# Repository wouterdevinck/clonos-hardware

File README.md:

#Clonos
**Open source network audio player**
by Wouter Devinck

##Repositories
 * **Hardware** (block diagram, schematic, pcb layout, ...): <br />
   https://github.com/wouterdevinck/clonos-hardware
 * Software (QT application, GStreamer interaction, ...): <br />
   https://github.com/wouterdevinck/clonos-application
 * Build system (Buildroot configuration files, kernel configuration, ...): <br />
   https://github.com/wouterdevinck/clonos-build
 * Android app: <br />
   https://github.com/wouterdevinck/clonos-android
 * Efforts to reverse engineer Spotify Connect: <br />
   https://github.com/wouterdevinck/clonos-poc-spotify

##Block diagram

##Prototype
*Status: boards ordered (December 1, 2015)*

Stack of four boards with all the components that have to end up on the final board.

###Protostack CPU
https://workspace.circuitmaker.com/Projects/B66F455D-E0F4-4F57-BF12-8FCD42A89455

###Protostack Power
https://workspace.circuitmaker.com/Projects/ADCA47EF-8110-4858-A632-40D1FB39EC8E

###Protostack Audio
https://workspace.circuitmaker.com/Projects/CEEC1620-CD76-49D0-8387-5E8A08206CBC

###Protostack Wifi
https://workspace.circuitmaker.com/Projects/3BDADFC3-9059-4C72-BE22-5D24FC84C105

##Final board
*Status: board design in progress*
https://workspace.circuitmaker.com/Projects/203E8A99-4B7F-4577-A6F3-57C3B201C072

##License
<br />This **hardware design** is licensed under a <a rel="license" href="http://creativecommons.org/licenses/by-sa/4.0/">Creative Commons Attribution-ShareAlike 4.0 International License</a>.

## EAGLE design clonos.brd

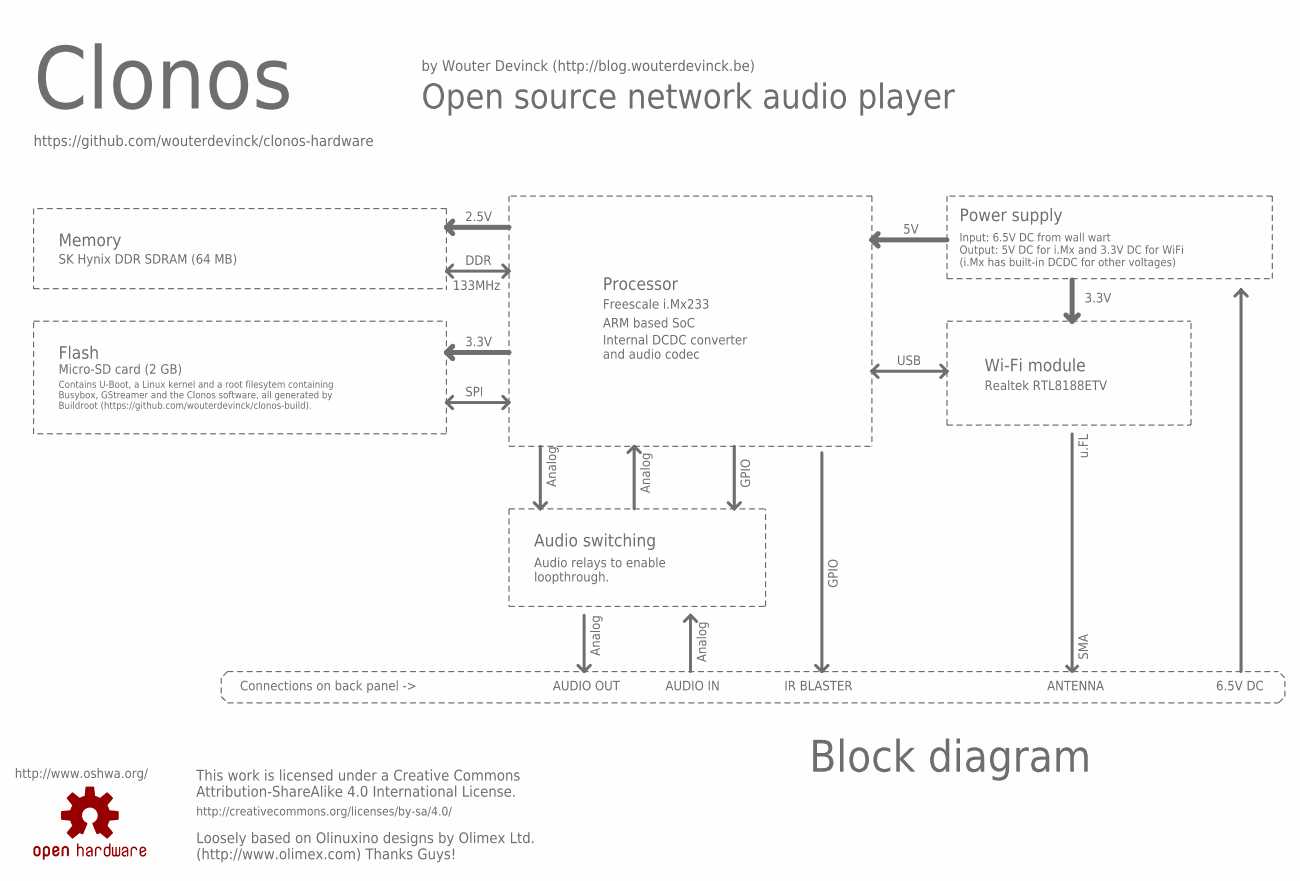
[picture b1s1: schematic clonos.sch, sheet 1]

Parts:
LOGO1: OSHW-LOGOS; OSHW-LOGO-S

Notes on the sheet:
Block diagram
Clonos
This work is licensed under a Creative Commons Attribution-ShareAlike 4.0 International License.
http://creativecommons.org/licenses/by-sa/4.0/
Open source network audio player
https://github.com/wouterdevinck/clonos-hardware
Loosely based on Olinuxino designs by Olimex Ltd. (http://www.olimex.com) Thanks Guys!
by Wouter Devinck (http://blog.wouterdevinck.be)
Power supply
Input: 6.5V DC from wall wart Output: 5V DC for i.Mx and 3.3V DC for WiFi (i.Mx has built-in DCDC for other voltages)
Processor
Freescale i.Mx233
Wi-Fi module
Flash
Memory
Audio switching
Realtek RTL8188ETV
Micro-SD card (2 GB)
Contains U-Boot, a Linux kernel and a root filesytem containing Busybox, GStreamer and the Clonos software, all generated by Buildroot (https://github.com/wouterdevinck/clonos-build).
SK Hynix DDR SDRAM (64 MB)
Audio relays to enable loopthrough.
6.5V DC
ANTENNA
IR BLASTER
AUDIO OUT
AUDIO IN
3.3V
USB
GPIO
Analog
2.5V
SPI
DDR
133MHz
Connections on back panel ->
u.FL
SMA
ARM based SoC
Internal DCDC converter and audio codec
http://www.oshwa.org/

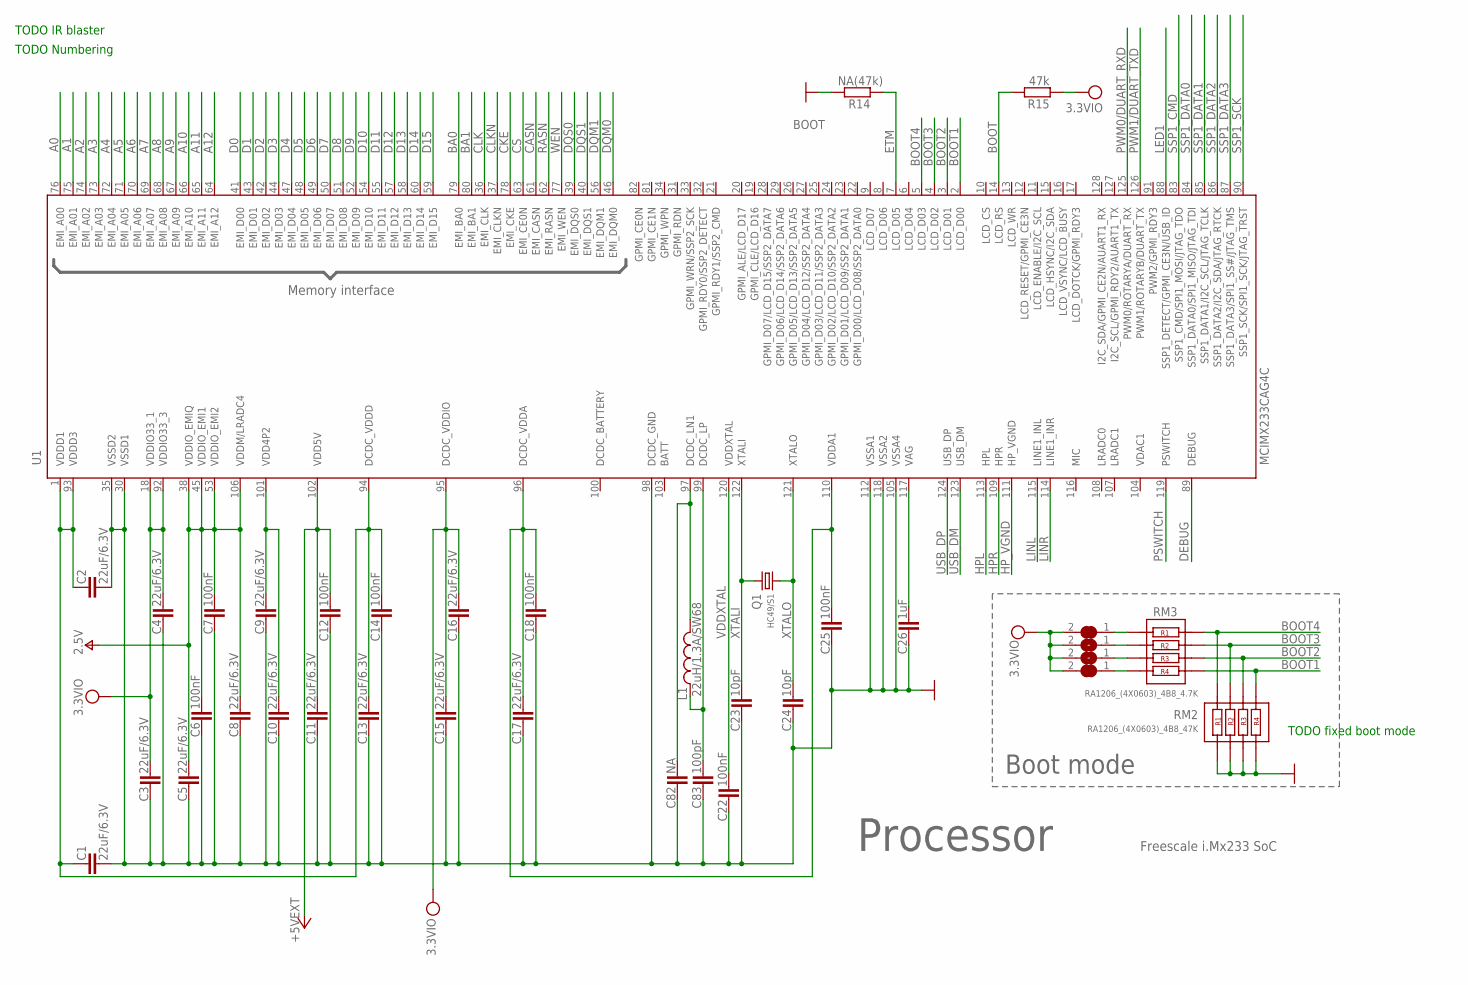
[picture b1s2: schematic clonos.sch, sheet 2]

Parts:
C1, C2, C3, C4, C5, C8, C9, C10, C11, C13, C15, C16, C17: 22uF/6.3V; C0805_5MIL_DWS
C6, C7, C12, C14, C18, C22, C25: 100nF; C0603_DWS
C23, C24: 10pF; C0603_DWS
C26: 1uF; C0603_DWS
C82: NA; C0603_DWS
C83: 100pF; C0603_DWS
D00_H, D03_H: Close; SJ_1_SMALLER
D01_H, D02_H: Open; SJ_1_SMALLER
L1: 22uH/1.3A/SW68; CD53
Q1: HC49/S1; HC49/SMD2_THIN
R14: NA(47k); R0603_5MIL_DWS
R15: 47k; R0603_5MIL_DWS
RM2: RA1206_(4X0603)_4B8_47K; R_MATRIX_4
RM3: RA1206_(4X0603)_4B8_4.7K; R_MATRIX_4
U1: MCIMX233CAG4C; TQFP128LD

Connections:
+5V: C11.2, C12.2, U1.102 (VDD5V); also elsewhere on the board
A0: U1.76 (EMI_A00); also elsewhere on the board
A1: U1.75 (EMI_A01); also elsewhere on the board
A2: U1.74 (EMI_A02); also elsewhere on the board
A3: U1.73 (EMI_A03); also elsewhere on the board
A4: U1.72 (EMI_A04); also elsewhere on the board
A5: U1.71 (EMI_A05); also elsewhere on the board
A6: U1.70 (EMI_A06); also elsewhere on the board
A7: U1.69 (EMI_A07); also elsewhere on the board
A8: U1.68 (EMI_A08); also elsewhere on the board
A9: U1.67 (EMI_A09); also elsewhere on the board
A10: U1.66 (EMI_A10); also elsewhere on the board
A11: U1.65 (EMI_A11); also elsewhere on the board
A12: U1.64 (EMI_A12); also elsewhere on the board
BA0: U1.79 (EMI_BA0); also elsewhere on the board
BA1: U1.80 (EMI_BA1); also elsewhere on the board
BOOT: R15.2, U1.14 (LCD_RS)
BOOT1: RM2.4.2, RM3.4.1, U1.2 (LCD_D00)
BOOT2: RM2.3.2, RM3.3.1, U1.3 (LCD_D01)
BOOT3: RM2.2.2, RM3.2.1, U1.4 (LCD_D02)
BOOT4: RM2.1.2, RM3.1.1, U1.5 (LCD_D03)
CASN: U1.61 (EMI_CASN); also elsewhere on the board
CKE: U1.78 (EMI_CKE); also elsewhere on the board
CLK: U1.36 (EMI_CLK); also elsewhere on the board
CLKN: U1.37 (EMI_CLKN); also elsewhere on the board
CS: U1.63 (EMI_CE0N); also elsewhere on the board
D0: U1.41 (EMI_D00); also elsewhere on the board
D1: U1.43 (EMI_D01); also elsewhere on the board
D2: U1.42 (EMI_D02); also elsewhere on the board
D3: U1.44 (EMI_D03); also elsewhere on the board
D4: U1.47 (EMI_D04); also elsewhere on the board
D5: U1.48 (EMI_D05); also elsewhere on the board
D6: U1.49 (EMI_D06); also elsewhere on the board
D7: U1.50 (EMI_D07); also elsewhere on the board
D8: U1.51 (EMI_D08); also elsewhere on the board
D9: U1.52 (EMI_D09); also elsewhere on the board
D10: U1.54 (EMI_D10); also elsewhere on the board
D11: U1.55 (EMI_D11); also elsewhere on the board
D12: U1.57 (EMI_D12); also elsewhere on the board
D13: U1.58 (EMI_D13); also elsewhere on the board
D14: U1.60 (EMI_D14); also elsewhere on the board
D15: U1.59 (EMI_D15); also elsewhere on the board
DCDC_BATTERY: U1.100 (DCDC_BATTERY)
DCDC_VDDA: C17.2, C18.2, C25.2, U1.96 (DCDC_VDDA), U1.110 (VDDA1)
DCDC_VDDD: C1.2, C2.2, C13.2, C14.2, U1.1 (VDDD1), U1.93 (VDDD3), U1.94 (DCDC_VDDD)
DEBUG: U1.89 (DEBUG); also elsewhere on the board
DQM0: U1.46 (EMI_DQM0); also elsewhere on the board
DQM1: U1.56 (EMI_DQM1); also elsewhere on the board
DQS0: U1.39 (EMI_DQS0); also elsewhere on the board
DQS1: U1.40 (EMI_DQS1); also elsewhere on the board
ETM: R14.2, U1.7 (LCD_D05)
GND: C1.1, C2.1, C3.1, C4.1, C5.1, C6.1, C7.1, C8.1, C9.1, C10.1, C11.1, C12.1, C13.1, C14.1, C15.1, C16.1, C17.1, C18.1, C22.1, C23.1, C24.1, C25.1, C26.1, C82.1, C83.1, R14.1, RM2.1.1, RM2.2.1, RM2.3.1, RM2.4.1, U1.30 (VSSD1), U1.35 (VSSD2), U1.98 (DCDC_GND), U1.105 (VSSA4), U1.112 (VSSA1), U1.118 (VSSA2); also elsewhere on the board
HPL: U1.113 (HPL); also elsewhere on the board
HPR: U1.109 (HPR); also elsewhere on the board
HP_VGND: U1.111 (HP_VGND); also elsewhere on the board
LED1: U1.88 (SSP1_DETECT/GPMI_CE3N/USB_ID); also elsewhere on the board
LINL: U1.115 (LINE1_INL); also elsewhere on the board
LINR: U1.114 (LINE1_INR); also elsewhere on the board
unnamed: C82.2, L1.2, U1.97 (DCDC_LN1)
unnamed: C83.2, L1.1, U1.99 (DCDC_LP)
unnamed: C26.2, U1.117 (VAG)
unnamed: D03_H.1, RM3.1.2
unnamed: D02_H.1, RM3.2.2
unnamed: D01_H.1, RM3.3.2
unnamed: D00_H.1, RM3.4.2
PSWITCH: U1.119 (PSWITCH); also elsewhere on the board
PWM0/DUART_RXD: U1.125 (PWM0/ROTARYA/DUART_RX); also elsewhere on the board
PWM1/DUART_TXD: U1.126 (PWM1/ROTARYB/DUART_TX); also elsewhere on the board
RASN: U1.62 (EMI_RASN); also elsewhere on the board
SSP1_CMD: U1.83 (SSP1_CMD/SPI1_MOSI/JTAG_TDO); also elsewhere on the board
SSP1_DATA0: U1.84 (SSP1_DATA0/SPI1_MISO/JTAG_TDI); also elsewhere on the board
SSP1_DATA1: U1.85 (SSP1_DATA1/I2C_SCL/JTAG_TCLK); also elsewhere on the board
SSP1_DATA2: U1.86 (SSP1_DATA2/I2C_SDA/JTAG_RTCK); also elsewhere on the board
SSP1_DATA3: U1.87 (SSP1_DATA3/SPI1_SS#/JTAG_TMS); also elsewhere on the board
SSP1_SCK: U1.90 (SSP1_SCK/SPI1_SCK/JTAG_TRST); also elsewhere on the board
USB_DM: U1.123 (USB_DM); also elsewhere on the board
USB_DP: U1.124 (USB_DP); also elsewhere on the board
V+: C5.2, C6.2, C7.2, C8.2, U1.38 (VDDIO_EMIQ), U1.45 (VDDIO_EMI1), U1.53 (VDDIO_EMI2), U1.106 (VDDM/LRADC4); also elsewhere on the board
VDD4P2: C9.2, C10.2, U1.101 (VDD4P2)
VDDXTAL: C22.2, U1.120 (VDDXTAL); also elsewhere on the board
VPP: C3.2, C4.2, C15.2, C16.2, D00_H.2, D01_H.2, D02_H.2, D03_H.2, R15.1, U1.18 (VDDIO33_1), U1.92 (VDDIO33_3), U1.95 (DCDC_VDDIO); also elsewhere on the board
WEN: U1.77 (EMI_WEN); also elsewhere on the board
XTALI: C23.2, Q1.2, U1.122 (XTALI); also elsewhere on the board
XTALO: C24.2, Q1.1, U1.121 (XTALO); also elsewhere on the board

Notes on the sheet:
TODO IR blaster
TODO Numbering
Processor
Memory interface
Freescale i.Mx233 SoC
Boot mode
TODO fixed boot mode

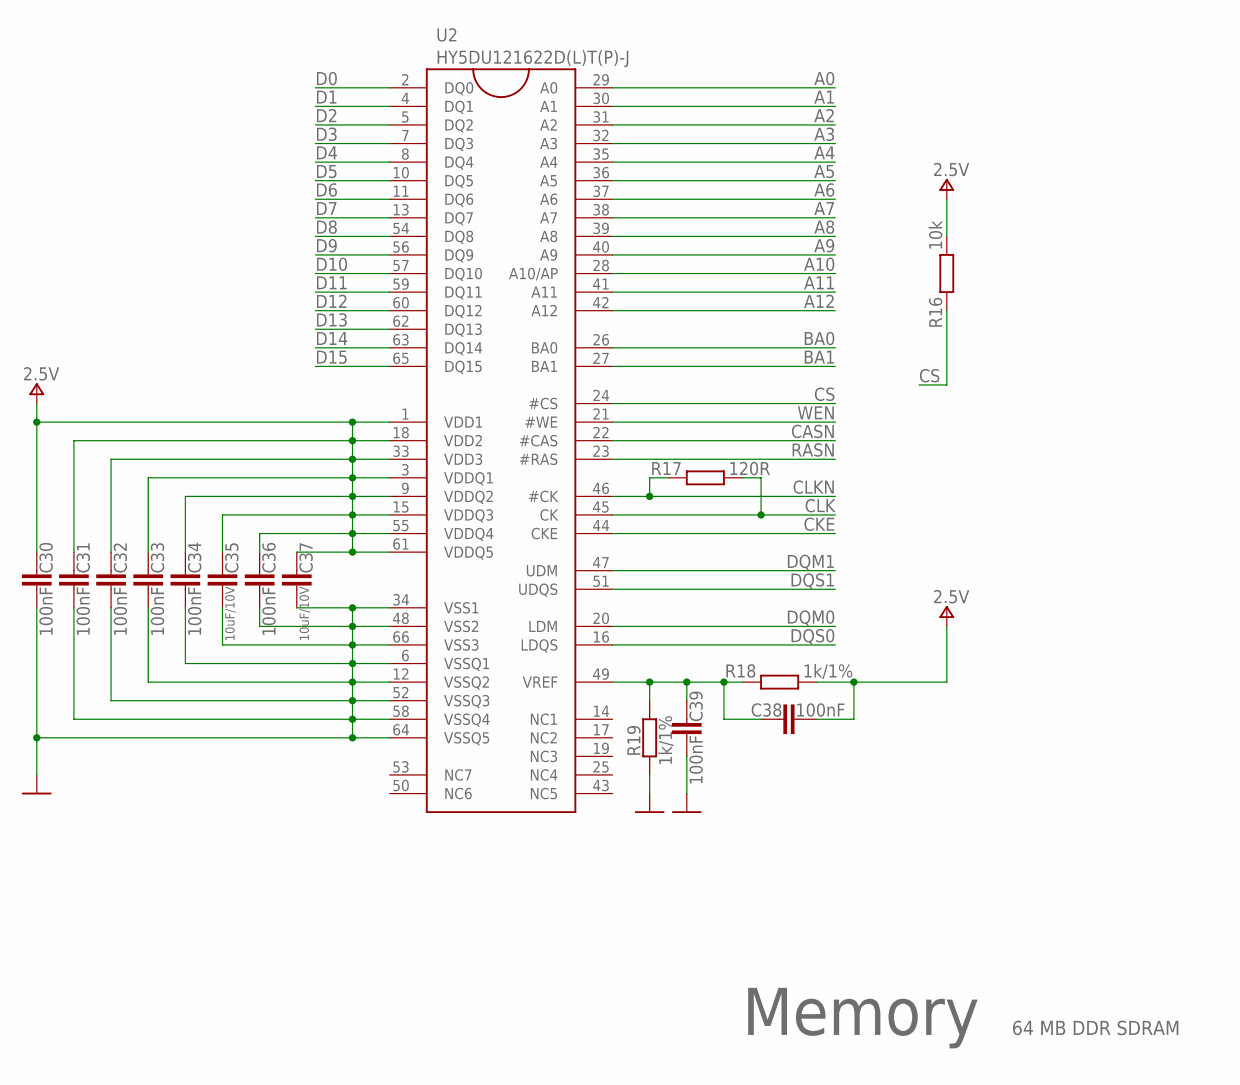
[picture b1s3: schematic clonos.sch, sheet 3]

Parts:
C30, C31, C32, C33, C34, C36, C38, C39: 100nF; C0603_DWS
C35, C37: 10uF/10V; C0603_DWS
R16: 10k; R0603_5MIL_DWS
R17: 120R; R0603_5MIL_DWS
R18, R19: 1k/1%; R0603_5MIL_DWS
U2: HY5DU121622D(L)T(P)-J; 66TSOP-II

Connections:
A0: U2.29 (A0); also elsewhere on the board
A1: U2.30 (A1); also elsewhere on the board
A2: U2.31 (A2); also elsewhere on the board
A3: U2.32 (A3); also elsewhere on the board
A4: U2.35 (A4); also elsewhere on the board
A5: U2.36 (A5); also elsewhere on the board
A6: U2.37 (A6); also elsewhere on the board
A7: U2.38 (A7); also elsewhere on the board
A8: U2.39 (A8); also elsewhere on the board
A9: U2.40 (A9); also elsewhere on the board
A10: U2.28 (A10/AP); also elsewhere on the board
A11: U2.41 (A11); also elsewhere on the board
A12: U2.42 (A12); also elsewhere on the board
BA0: U2.26 (BA0); also elsewhere on the board
BA1: U2.27 (BA1); also elsewhere on the board
CASN: U2.22 (#CAS); also elsewhere on the board
CKE: U2.44 (CKE); also elsewhere on the board
CLK: R17.2, U2.45 (CK); also elsewhere on the board
CLKN: R17.1, U2.46 (#CK); also elsewhere on the board
CS: R16.1, U2.24 (#CS); also elsewhere on the board
D0: U2.2 (DQ0); also elsewhere on the board
D1: U2.4 (DQ1); also elsewhere on the board
D2: U2.5 (DQ2); also elsewhere on the board
D3: U2.7 (DQ3); also elsewhere on the board
D4: U2.8 (DQ4); also elsewhere on the board
D5: U2.10 (DQ5); also elsewhere on the board
D6: U2.11 (DQ6); also elsewhere on the board
D7: U2.13 (DQ7); also elsewhere on the board
D8: U2.54 (DQ8); also elsewhere on the board
D9: U2.56 (DQ9); also elsewhere on the board
D10: U2.57 (DQ10); also elsewhere on the board
D11: U2.59 (DQ11); also elsewhere on the board
D12: U2.60 (DQ12); also elsewhere on the board
D13: U2.62 (DQ13); also elsewhere on the board
D14: U2.63 (DQ14); also elsewhere on the board
D15: U2.65 (DQ15); also elsewhere on the board
DQM0: U2.20 (LDM); also elsewhere on the board
DQM1: U2.47 (UDM); also elsewhere on the board
DQS0: U2.16 (LDQS); also elsewhere on the board
DQS1: U2.51 (UDQS); also elsewhere on the board
GND: C30.1, C31.1, C32.1, C33.1, C34.1, C35.1, C36.1, C37.1, C39.1, R19.1, U2.6 (VSSQ1), U2.12 (VSSQ2), U2.34 (VSS1), U2.48 (VSS2), U2.52 (VSSQ3), U2.58 (VSSQ4), U2.64 (VSSQ5), U2.66 (VSS3); also elsewhere on the board
unnamed: C38.2, C39.2, R18.1, R19.2, U2.49 (VREF)
RASN: U2.23 (#RAS); also elsewhere on the board
V+: C30.2, C31.2, C32.2, C33.2, C34.2, C35.2, C36.2, C37.2, C38.1, R16.2, R18.2, U2.1 (VDD1), U2.3 (VDDQ1), U2.9 (VDDQ2), U2.15 (VDDQ3), U2.18 (VDD2), U2.33 (VDD3), U2.55 (VDDQ4), U2.61 (VDDQ5); also elsewhere on the board
WEN: U2.21 (#WE); also elsewhere on the board

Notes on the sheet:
Memory
64 MB DDR SDRAM

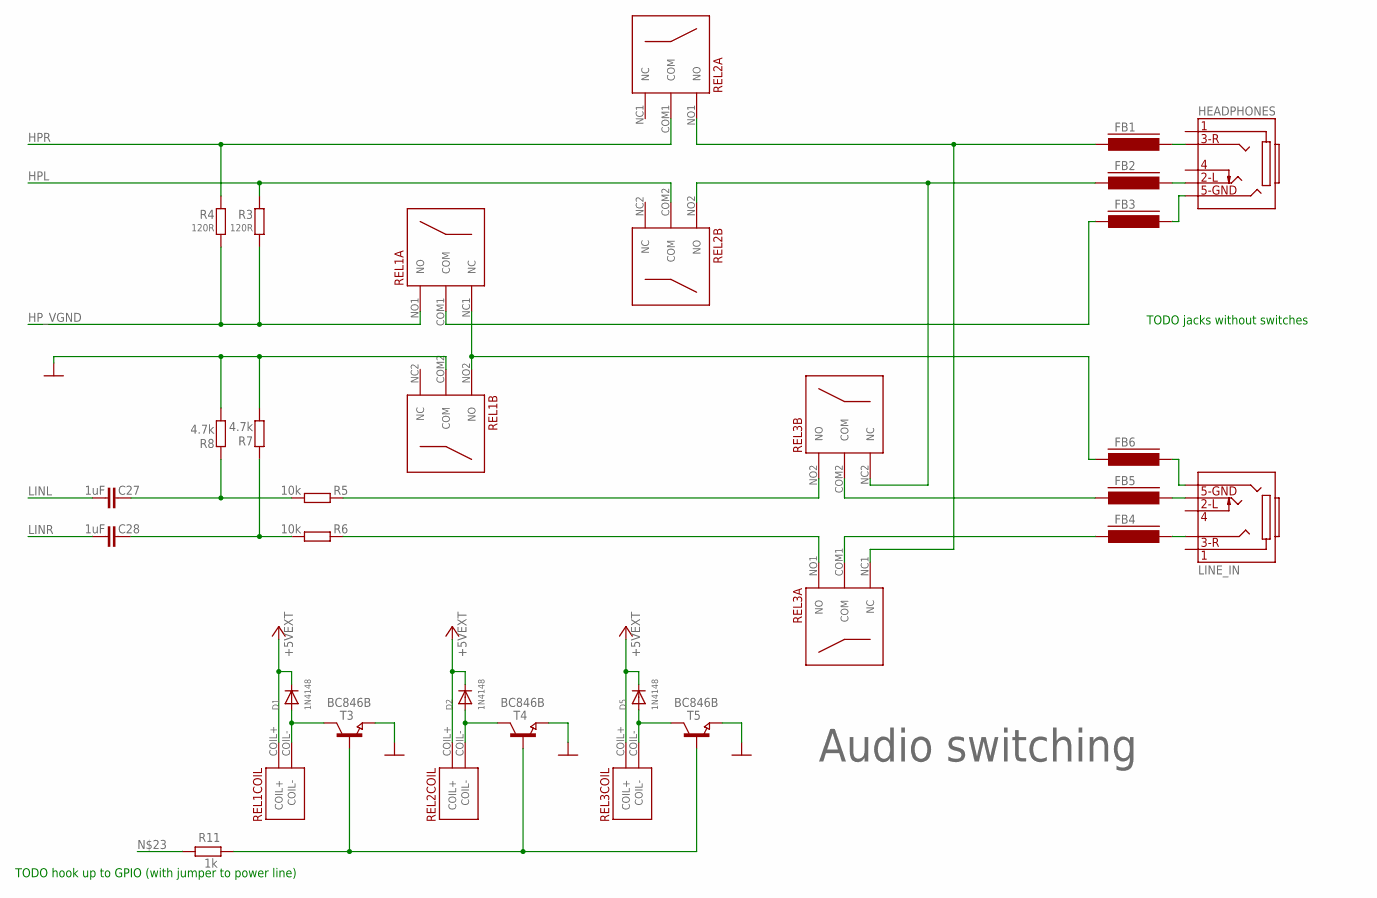
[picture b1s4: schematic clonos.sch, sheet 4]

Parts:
C27, C28: 1uF; C0603_DWS
D1, D2, D5: 1N4148; SOD-323F
FB1, FB2, FB3, FB4, FB5, FB6: HZ0805D152R; FB805
HEADPHONES: AUDIO_JACK_5PINPJ-W47S-05D2-LF_V2; PJ-W47S-05D2-LF_5PIN_V2
LINE_IN: AUDIO_JACK_5PINPJ-W47S-05D2-LF_V2; PJ-W47S-05D2-LF_5PIN_V2
R3, R4: 120R; R0603_5MIL_DWS
R5, R6: 10k; R0603_5MIL_DWS
R7, R8: 4.7k; R0603_5MIL_DWS
R11: 1k; R0603_5MIL_DWS
REL1, REL2, REL3: A5W-K-BIS; A5W-K
T3, T4, T5: BC846B; SOT23

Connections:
+5V: D1.C, D2.C, D5.C, REL1.COIL+, REL2.COIL+, REL3.COIL+; also elsewhere on the board
GND: R7.1, R8.1, REL1.COM2 (COM), T3.2 (E), T4.2 (E), T5.2 (E); also elsewhere on the board
HPL: R3.2, REL2.COM2 (COM); also elsewhere on the board
HPR: R4.2, REL2.COM1 (COM); also elsewhere on the board
HP_VGND: R3.1, R4.1, REL1.NO1 (NO); also elsewhere on the board
LINL: C27.2; also elsewhere on the board
LINR: C28.2; also elsewhere on the board
unnamed: R6.2, REL3.NO1 (NO)
unnamed: FB1.2, REL2.NO1 (NO), REL3.NC1 (NC)
unnamed: FB2.2, REL2.NO2 (NO), REL3.NC2 (NC)
unnamed: FB5.2, REL3.COM2 (COM)
unnamed: R5.2, REL3.NO2 (NO)
unnamed: FB4.2, REL3.COM1 (COM)
unnamed: FB3.2, REL1.COM1 (COM)
unnamed: FB1.1, HEADPHONES.3
unnamed: FB6.2, REL1.NC1 (NC), REL1.NO2 (NO)
unnamed: FB2.1, HEADPHONES.2
unnamed: FB3.1, HEADPHONES.5
unnamed: FB5.1, LINE_IN.2
unnamed: FB4.1, LINE_IN.3
unnamed: FB6.1, LINE_IN.5
unnamed: D1.A, REL1.COIL-, T3.3 (C)
unnamed: D2.A, REL2.COIL-, T4.3 (C)
unnamed: R11.2, T3.1 (B), T4.1 (B), T5.1 (B)
unnamed: D5.A, REL3.COIL-, T5.3 (C)
unnamed: C28.1, R6.1, R7.2
unnamed: C27.1, R5.1, R8.2

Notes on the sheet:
Audio switching
TODO jacks without switches
TODO hook up to GPIO (with jumper to power line)

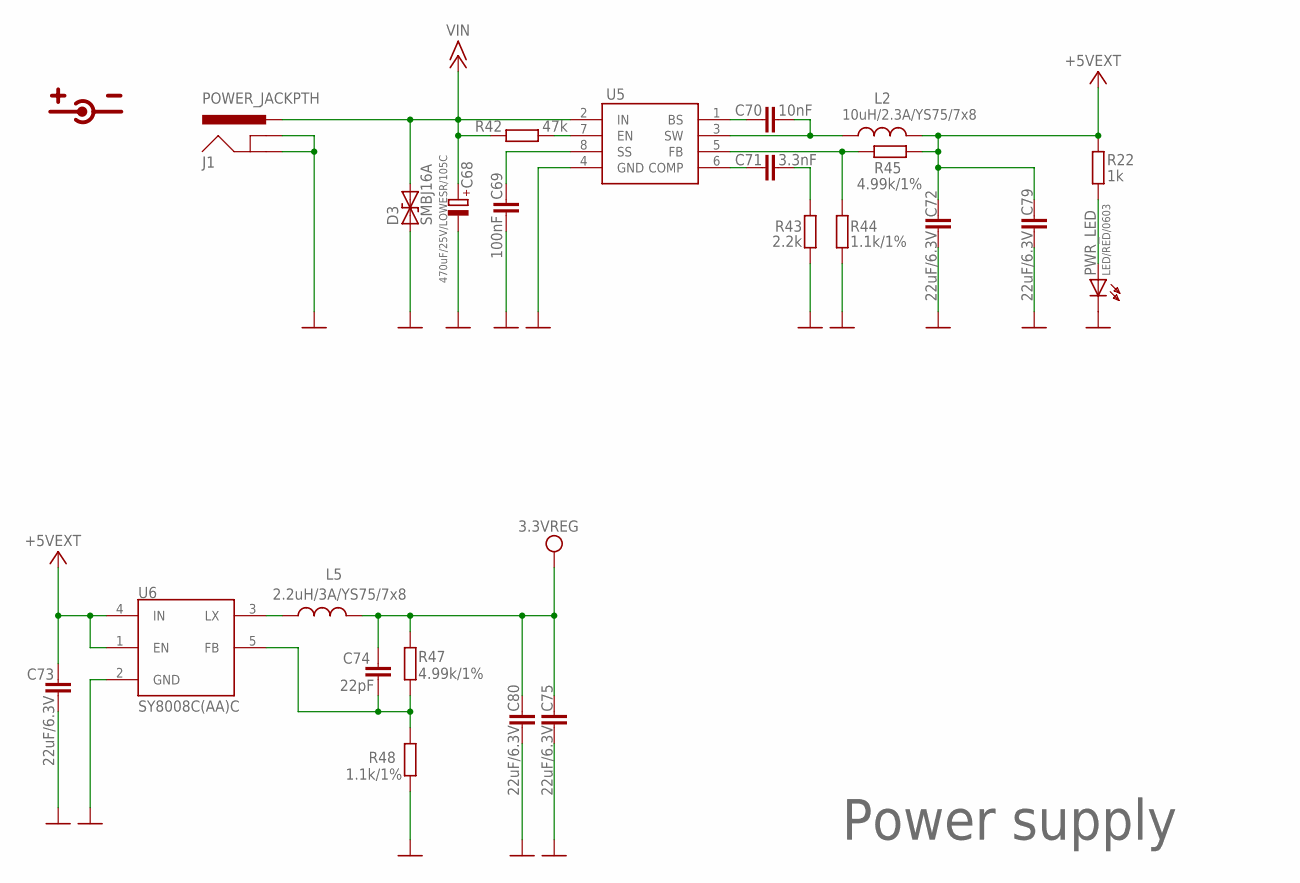
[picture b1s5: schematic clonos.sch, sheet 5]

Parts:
C68: 470uF/25V/LOWESR/105C; E5-10,5
C69: 100nF; C0603_DWS
C70: 10nF; C0603_DWS
C71: 3.3nF; C0603_DWS
C72, C73, C75, C79, C80: 22uF/6.3V; C0805_5MIL_DWS
C74: 22pF; C0603_DWS
D3: SMBJ16A; DO214AA
J1: POWER_JACKPTH; POWER_JACK_PTH
L2: 10uH/2.3A/YS75/7x8; 8X8MM_3131
L5: 2.2uH/3A/YS75/7x8; 8X8MM_3131
PWR_LED: LED/RED/0603; LED-0603
R22: 1k; R0603_5MIL_DWS
R42: 47k; R0603_5MIL_DWS
R43: 2.2k; R0603_5MIL_DWS
R44, R48: 1.1k/1%; R0603_5MIL_DWS
R45, R47: 4.99k/1%; R0603_5MIL_DWS
U5: MP1482DS; SOIC8
U6: SY8008C(AA)C; SOT23-5

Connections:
+5V: C72.1, C73.1, C79.1, L2.2, R22.1, R45.2, U6.1 (EN), U6.4 (IN); also elsewhere on the board
+15V: C68.+, D3.C (2), J1.PWR, R42.1, U5.2 (IN)
GND: C68.-, C69.2, C72.2, C73.2, C75.2, C79.2, C80.2, D3.A (1), J1.GND, J1.GNDBREAK, PWR_LED.C, R43.2, R44.2, R48.2, U5.4 (GND), U6.2 (GND); also elsewhere on the board
unnamed: C69.1, U5.8 (SS)
unnamed: R42.2, U5.7 (EN)
unnamed: C70.1, U5.1 (BS)
unnamed: C70.2, L2.1, U5.3 (SW)
unnamed: C71.1, U5.6 (COMP)
unnamed: C71.2, R43.1
unnamed: R44.1, R45.1, U5.5 (FB)
unnamed: L5.1, U6.3 (LX)
unnamed: C74.2, R47.2, R48.1, U6.5 (FB)
unnamed: PWR_LED.A, R22.2
VCC: C74.1, C75.1, C80.1, L5.2, R47.1; also elsewhere on the board

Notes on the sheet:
Power supply

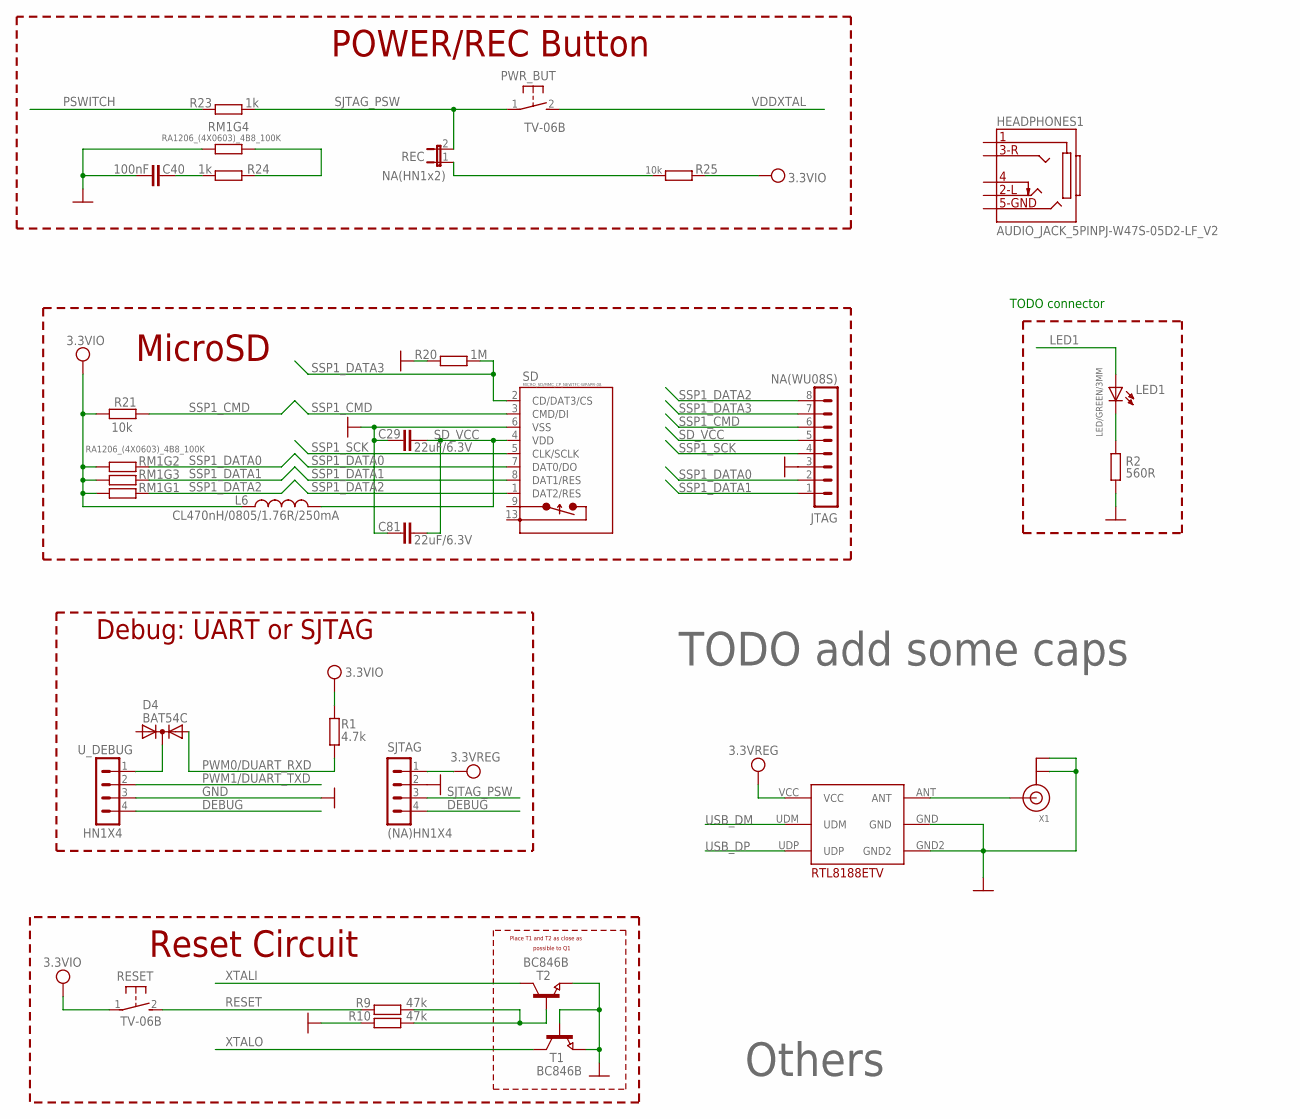
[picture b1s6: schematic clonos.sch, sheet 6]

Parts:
C29, C81: 22uF/6.3V; C0805_5MIL_DWS
C40: 100nF; C0603_DWS
D4: BAT54C; SOT23C
HEADPHONES1: AUDIO_JACK_5PINPJ-W47S-05D2-LF_V2; PJ-W47S-05D2-LF_5PIN_V2
JTAG: NA(WU08S); WU08S
L6: CL470nH/0805/1.76R/250mA; L0805_5MIL_DWS
LED1: LED/GREEN/3MM; LED-3.0MM
PWR_BUT: TV-06B; B3F-31XX
R1: 4.7k; R0603_5MIL_DWS
R2: 560R; R0603_5MIL_DWS
R9, R10: 47k; R0603_5MIL_DWS
R20: 1M; R0603_5MIL_DWS
R21: 10k; R0603_5MIL_DWS
R23, R24: 1k; R0603_5MIL_DWS
R25: 10k; R0603_5MIL_DWS_NA
REC: NA(HN1x2); JP1
RESET: TV-06B; B3F-31XX
RM1: RA1206_(4X0603)_4B8_100K; R_MATRIX_4
SD: MICRO_SD/MMC_CP_NEWTFC-WPAPR-08; TFC-WPAPR-08
SJTAG: (NA)HN1X4; HN1X4
T1, T2: BC846B; SOT23
U$1: RTL8188ETV
U_DEBUG: HN1X4
X1: ANTENNA_U.FL; U.FL

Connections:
DEBUG: SJTAG.4, U_DEBUG.4; also elsewhere on the board
GND: C29.1, C40.2, C81.1, JTAG.3, R2.1, R10.2, R20.2, RM1.4.1 (1), SD.6 (VSS), SJTAG.2, T1.1 (B), T1.2 (E), T2.2 (E), U$1.GND, U$1.GND2, U_DEBUG.3, X1.1 (GND), X1.2 (GND); also elsewhere on the board
LED1: LED1.A; also elsewhere on the board
unnamed: U$1.ANT, X1.3 (SIGNAL)
unnamed: R25.1, REC.1
unnamed: R24.2, RM1.4.2 (2)
unnamed: D4.3 (K), U_DEBUG.1
unnamed: C40.1, R24.1
unnamed: LED1.K (C), R2.2
unnamed: R9.1, R10.1, T2.1 (B)
PSWITCH: R23.1; also elsewhere on the board
PWM0/DUART_RXD: D4.1 (A1), R1.1; also elsewhere on the board
PWM1/DUART_TXD: U_DEBUG.2; also elsewhere on the board
RESET: R9.2, RESET.2 (S)
SD_VCC: C29.2, C81.2, JTAG.5, L6.2, SD.4 (VDD)
SJTAG_PSW: PWR_BUT.1, R23.2, REC.2, SJTAG.3
SSP1_CMD: JTAG.6, R21.1, SD.3 (CMD/DI); also elsewhere on the board
SSP1_DATA0: JTAG.2, RM1.2.1 (1), SD.7 (DAT0/DO); also elsewhere on the board
SSP1_DATA1: JTAG.1, RM1.3.1 (1), SD.8 (DAT1/RES); also elsewhere on the board
SSP1_DATA2: JTAG.8, RM1.1.1 (1), SD.1 (DAT2/RES); also elsewhere on the board
SSP1_DATA3: JTAG.7, R20.1, SD.2 (CD/DAT3/CS); also elsewhere on the board
SSP1_SCK: JTAG.4, SD.5 (CLK/SCLK); also elsewhere on the board
USB_DM: U$1.UDM; also elsewhere on the board
USB_DP: U$1.UDP; also elsewhere on the board
VCC: SJTAG.1, U$1.VCC; also elsewhere on the board
VDDXTAL: PWR_BUT.2 (S); also elsewhere on the board
VPP: L6.1, R1.2, R21.2, R25.2, RESET.1, RM1.1.2 (2), RM1.2.2 (2), RM1.3.2 (2); also elsewhere on the board
XTALI: T2.3 (C); also elsewhere on the board
XTALO: T1.3 (C); also elsewhere on the board

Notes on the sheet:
Others
Place T1 and T2 as close as
possible to Q1
Reset Circuit
MicroSD
POWER/REC Button
Debug: UART or SJTAG
TODO connector
TODO add some caps

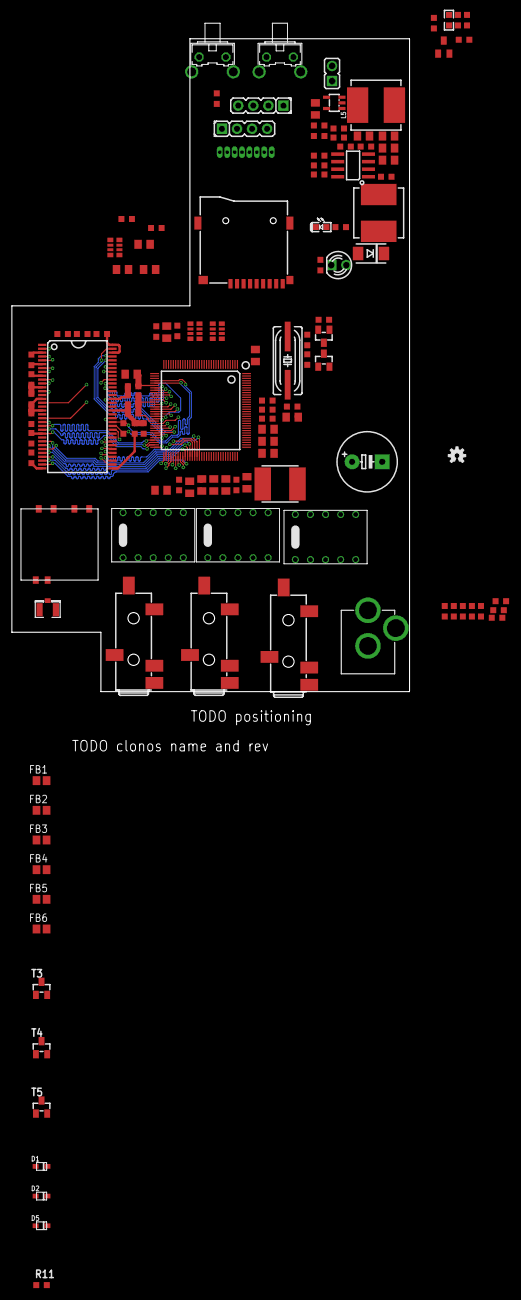
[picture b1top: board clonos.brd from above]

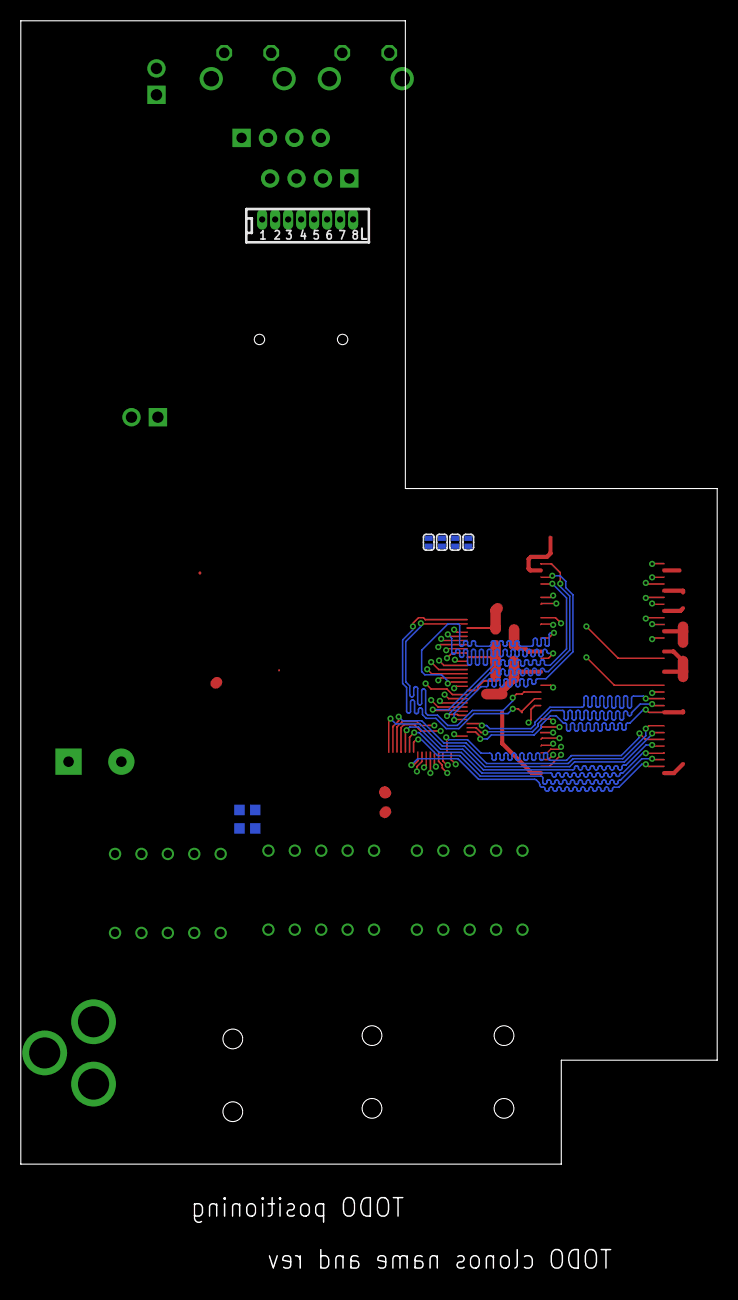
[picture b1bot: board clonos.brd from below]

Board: 4 copper layers, 67.0 x 121.1 mm, 133 parts (10 on the bottom side), 126 nets.

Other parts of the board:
U$5: LOGO-OPENHARDWARE_8X8
U$10: ESD_SYMBOL
U$11: RECYCLE_BIN1/8

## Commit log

2014-10-05 Early version of schematic and pcb layout. Work in progress.
2014-10-24 Some work on the schematic
2014-10-25 Audio switching
2015-12-02 Prototype images and gerbers

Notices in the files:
parts and their libraries:
SparkFun-Aesthetics: Licensing: CC v3.0 Share-Alike You are welcome to use this library for commercial purposes.
